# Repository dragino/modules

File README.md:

Modules
=======

What you can find in this directory:

- **Hardware** - Schematic and PCB files for modules or nodes. The eagle SCH and PCB files need to be downloaded as ZIP in this directory. Otherwise there will be issue when open in Eagle.

- **Libraries** - Libraries use for modules. 
  
- **Examples** - Examples source code to shows how to use the modules/nodes.

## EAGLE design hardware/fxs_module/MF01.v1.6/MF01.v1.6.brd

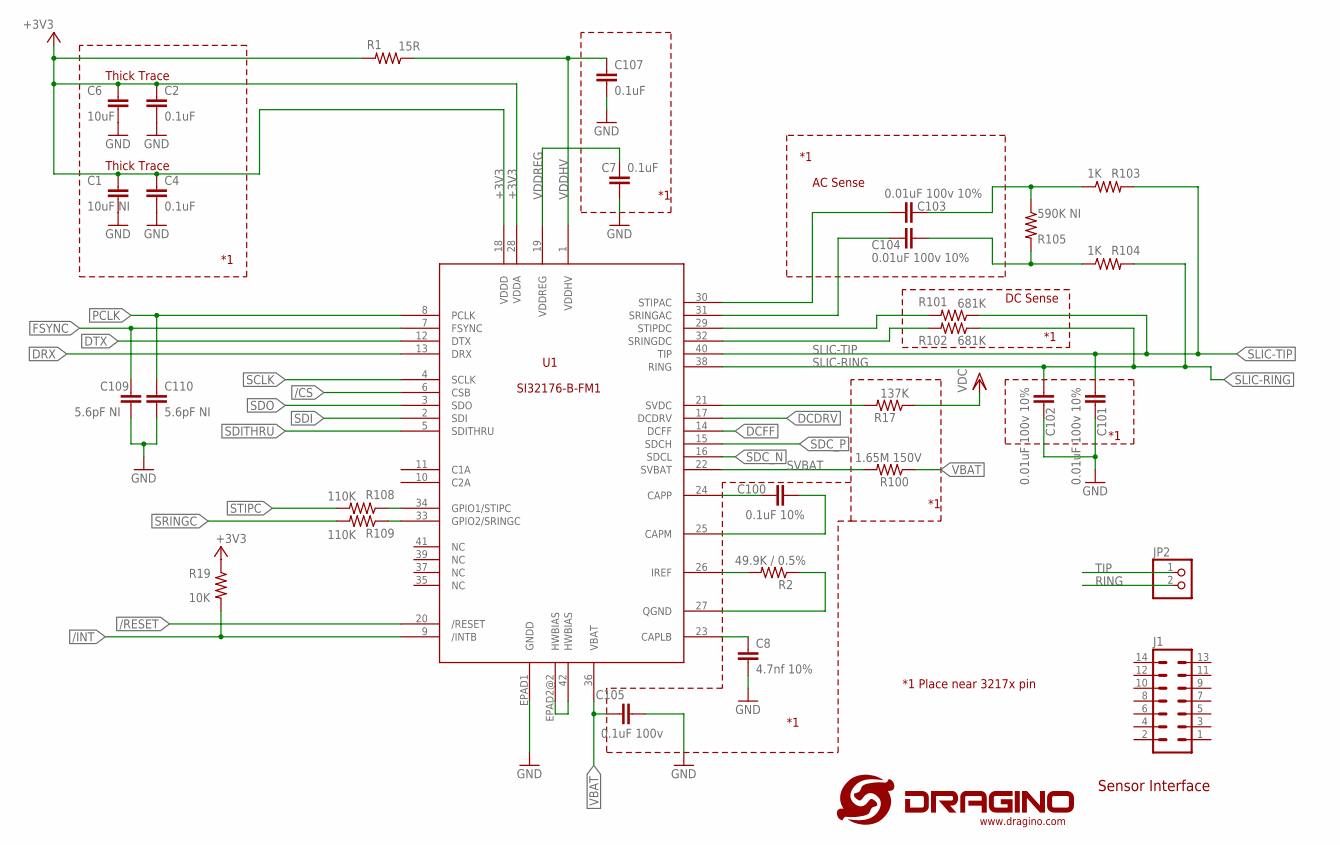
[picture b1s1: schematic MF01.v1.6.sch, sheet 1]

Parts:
C1: 10uF NI; C0603
C2, C4, C7, C107: 0.1uF; C0402
C6: 10uF; C0603
C8: 4.7nf 10%; C0402
C100: 0.1uF 10%; C0402
C101, C102, C103, C104: 0.01uF 100v 10%; C0603
C105: 0.1uF 100v; C0603
C109, C110: 5.6pF NI; C0402
J1: MA07-2
JP2: PINHD-1X2; 1X02
R1: 15R; R0805
R2: 49.9K / 0.5%; R0402
R17: 137K; R0402
R19: 10K; R0402
R100: 1.65M 150V; R0805
R101, R102: 681K; R0805
R103, R104: 1K; R0603
R105: 590K NI; R0805
R108, R109: 110K; R0402
U1: SI32176-B-FM1; SI3217X-QFN42

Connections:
+3V3: C1.2, C2.2, C4.2, C6.2, R1.2, R19.1, U1.18 (VDDD), U1.28 (VDDA); also elsewhere on the board
/CS: U1.6 (CSB); also elsewhere on the board
/INT: R19.2, U1.9 (/INTB); also elsewhere on the board
/RESET: U1.20 (/RESET); also elsewhere on the board
DCDRV: U1.17 (DCDRV); also elsewhere on the board
DCFF: U1.14 (DCFF); also elsewhere on the board
DRX: U1.13 (DRX); also elsewhere on the board
DTX: U1.12 (DTX); also elsewhere on the board
EPAD2: U1.42 (HWBIAS), U1.EPAD2@2 (HWBIAS)
FSYNC: C109.2, U1.7 (FSYNC); also elsewhere on the board
GND: C1.1, C2.1, C4.1, C6.1, C7.1, C8.2, C101.2, C102.2, C105.1, C107.1, C109.1, C110.1, U1.EPAD1 (GNDD); also elsewhere on the board
unnamed: R102.2, U1.32 (SRINGDC)
unnamed: R2.2, U1.26 (IREF)
unnamed: C8.1, U1.23 (CAPLB)
unnamed: R2.1, U1.27 (QGND)
unnamed: C100.1, U1.24 (CAPP)
unnamed: C100.2, U1.25 (CAPM)
unnamed: R101.2, U1.29 (STIPDC)
unnamed: C104.1, U1.31 (SRINGAC)
unnamed: C103.1, U1.30 (STIPAC)
unnamed: C104.2, R104.1, R105.2
unnamed: C103.2, R103.1, R105.1
unnamed: R17.2, U1.21 (SVDC)
unnamed: R108.1, U1.34 (GPIO1/STIPC)
unnamed: R109.1, U1.33 (GPIO2/SRINGC)
PCLK: C110.2, U1.8 (PCLK); also elsewhere on the board
RING: JP2.2; also elsewhere on the board
SCLK: U1.4 (SCLK); also elsewhere on the board
SDC_N: U1.16 (SDCL); also elsewhere on the board
SDC_P: U1.15 (SDCH); also elsewhere on the board
SDI: U1.2 (SDI); also elsewhere on the board
SDITHRU: U1.5 (SDITHRU)
SDO: U1.3 (SDO); also elsewhere on the board
SLIC-RING: C102.1, R102.1, R104.2, U1.38 (RING); also elsewhere on the board
SLIC-TIP: C101.1, R101.1, R103.2, U1.40 (TIP); also elsewhere on the board
SRINGC: R109.2; also elsewhere on the board
STIPC: R108.2; also elsewhere on the board
SVBAT: R100.2, U1.22 (SVBAT)
TIP: JP2.1; also elsewhere on the board
VBAT: C105.2, R100.1, U1.36 (VBAT); also elsewhere on the board
VDC: R17.1; also elsewhere on the board
VDDHV: C107.2, R1.1, U1.1 (VDDHV)
VDDREG: C7.2, U1.19 (VDDREG)

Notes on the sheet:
Sensor Interface
*1 Place near 3217x pin
DC Sense
AC Sense
Thick Trace

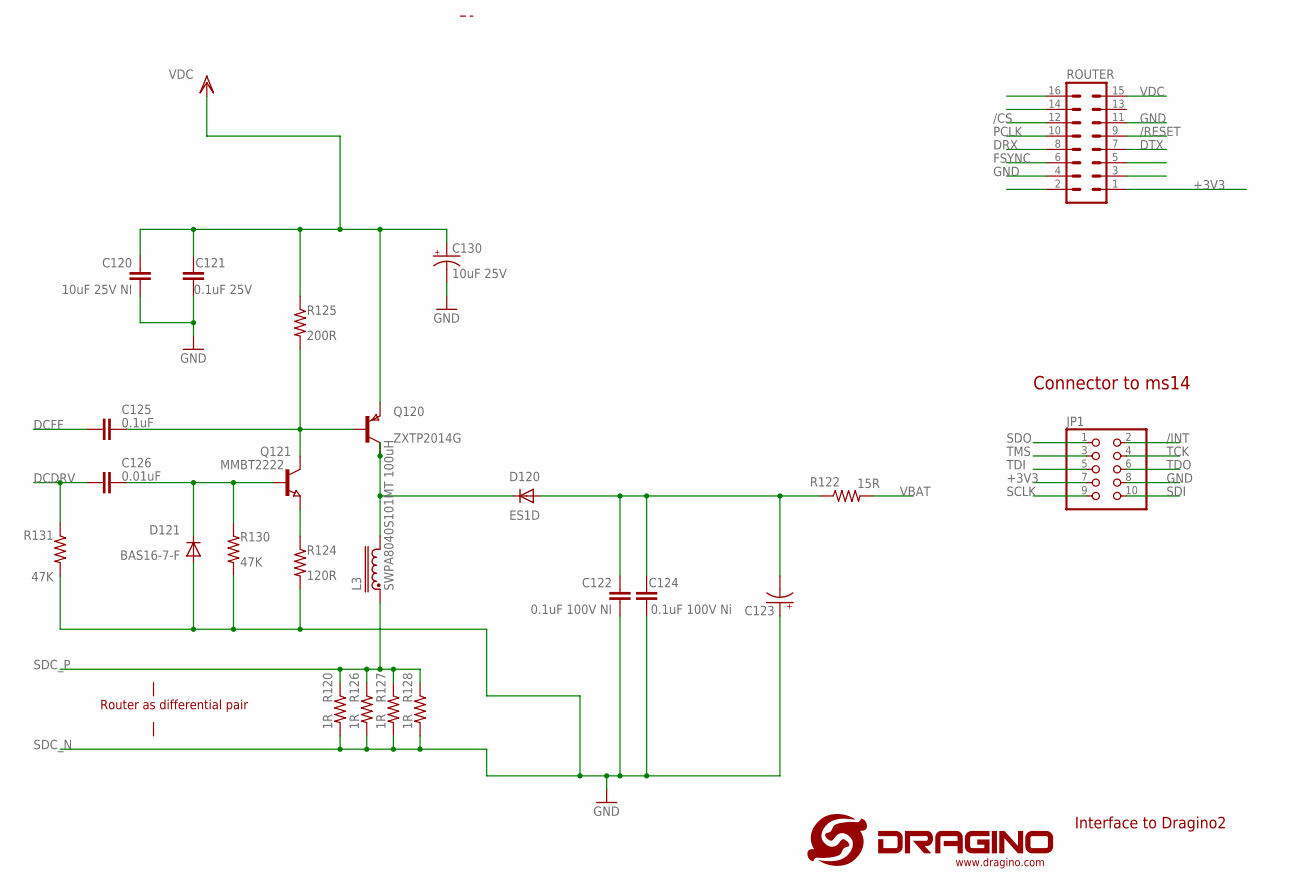
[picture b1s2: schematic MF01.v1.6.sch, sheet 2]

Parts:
C120: 10uF 25V NI; C1206
C121: 0.1uF 25V; C0402
C122: 0.1uF 100V NI; C0603
C123: CPOL-US153CLV-0605; 153CLV-0605
C124: 0.1uF 100V Ni; C0603
C125: 0.1uF; C0402
C126: 0.01uF; C0402
C130: 10uF 25V; UD-4X5,8_NICHICON
D120: ES1D; SOD-123_MINI-SMA
D121: BAS16-7-F; SOT23
JP1: PINHD-2X5_2.00; 2X05M
L3: SWPA8040S101MT 100uH; LVS808040
Q120: ZXTP2014G; SOT223
Q121: MMBT2222; SOT23
R120, R126, R127, R128: 1R; R0402
R122: 15R; R0805
R124: 120R; R0402
R125: 200R; R0603
R130, R131: 47K; R0402
ROUTER: MA08-2
U$5: LOGO-NEW; LOGO-SILK-NEW

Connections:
+3V3: JP1.7, ROUTER.1; also elsewhere on the board
/CS: ROUTER.12; also elsewhere on the board
/INT: JP1.2; also elsewhere on the board
/RESET: ROUTER.9; also elsewhere on the board
DCDRV: C126.2, R131.1; also elsewhere on the board
DCFF: C125.2; also elsewhere on the board
DRX: ROUTER.8; also elsewhere on the board
DTX: ROUTER.7; also elsewhere on the board
FSYNC: ROUTER.6; also elsewhere on the board
GND: C120.2, C121.2, C122.2, C123.+, C124.2, C130.-, D121.1 (A), JP1.8, R124.2, R130.2, R131.2, ROUTER.4, ROUTER.11; also elsewhere on the board
unnamed: C126.1, D121.3 (C), Q121.1 (B), R130.1
unnamed: Q121.2 (E), R124.1
unnamed: C125.1, Q120.1 (B), Q121.3 (C), R125.2
unnamed: D120.C, L3.P$2 (4), Q120.2 (C), Q120.4 (C)
unnamed: C122.1, C123.-, C124.1, D120.A, R122.1
PCLK: ROUTER.10; also elsewhere on the board
SCLK: JP1.9; also elsewhere on the board
SDC_N: R120.2, R126.2, R127.2, R128.2; also elsewhere on the board
SDC_P: L3.P$1 (1), R120.1, R126.1, R127.1, R128.1; also elsewhere on the board
SDI: JP1.10; also elsewhere on the board
SDO: JP1.1; also elsewhere on the board
TCK: JP1.4
TDI: JP1.5
TDO: JP1.6
TMS: JP1.3
VBAT: R122.2; also elsewhere on the board
VDC: C120.1, C121.1, C130.+, Q120.3 (E), R125.1, ROUTER.15; also elsewhere on the board

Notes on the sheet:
Interface to Dragino2
Connector to ms14
Router as differential pair

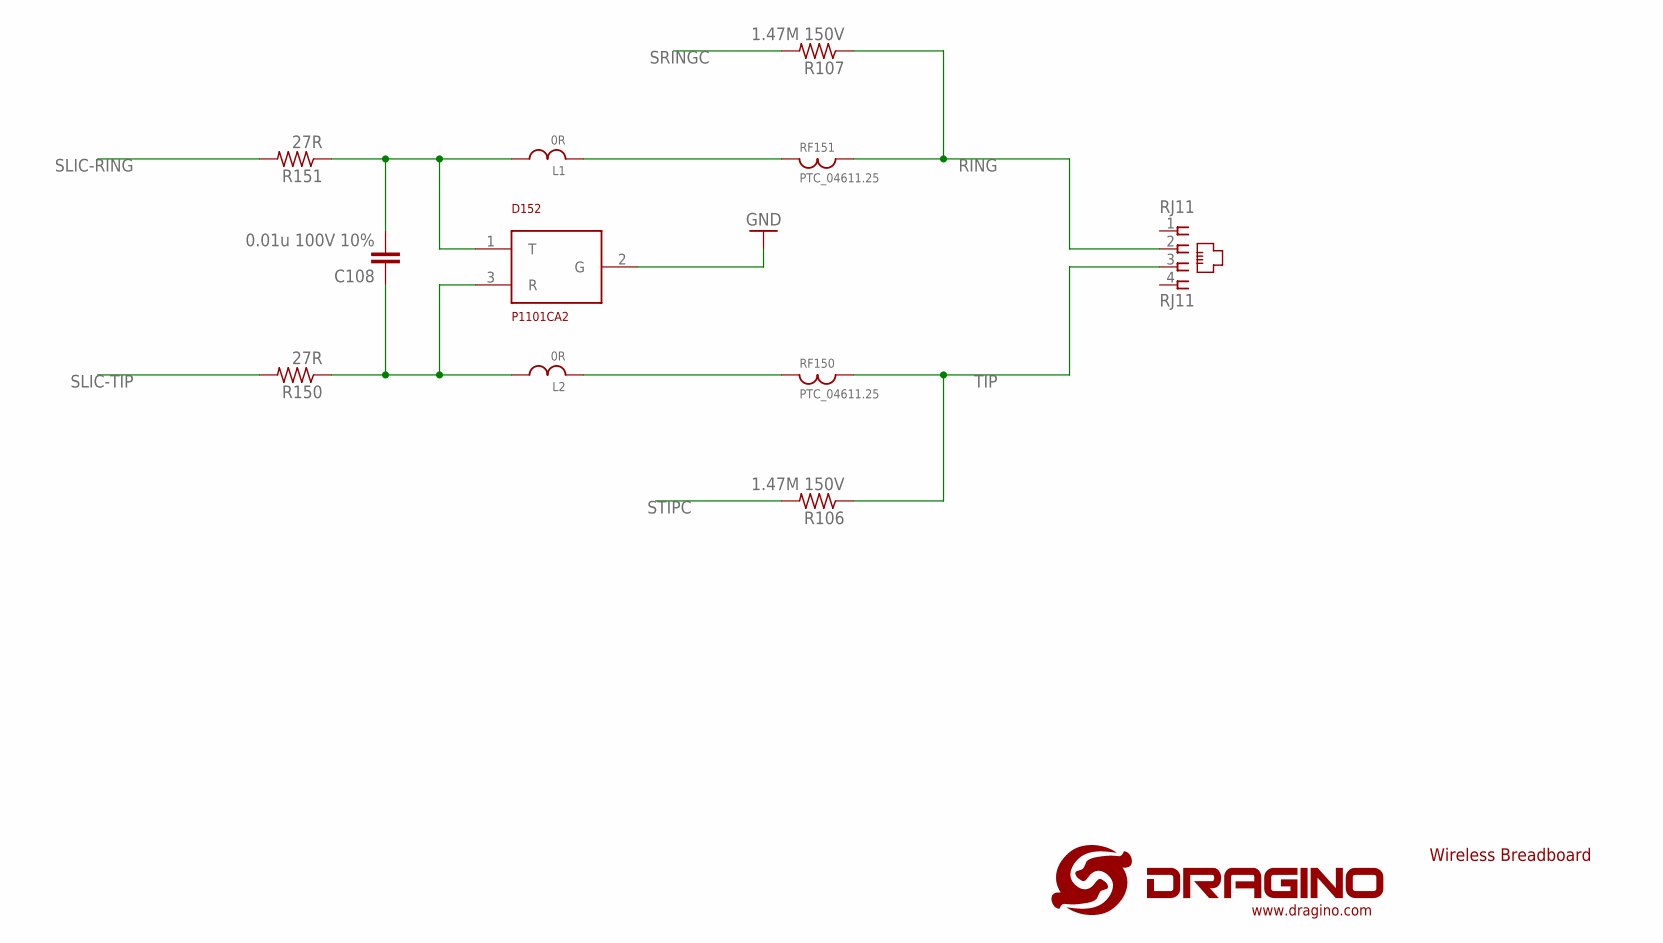
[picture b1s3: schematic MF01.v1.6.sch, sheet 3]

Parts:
C108: 0.01u 100V 10%; C0603
D152: P1101CA2; DO-214
L1, L2: 0R; C0805
R106, R107: 1.47M 150V; R1206
R150, R151: 27R; R0805
RF150, RF151: PTC_04611.25; 04611.25
RJ11: RJ11; 14867

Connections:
GND: D152.2 (G); also elsewhere on the board
unnamed: L1.1, RF151.P1
unnamed: L2.1, RF150.P1
unnamed: C108.1, D152.3 (R), L2.2, R150.1
unnamed: C108.2, D152.1 (T), L1.2, R151.1
RING: R107.1, RF151.P2, RJ11.2; also elsewhere on the board
SLIC-RING: R151.2; also elsewhere on the board
SLIC-TIP: R150.2; also elsewhere on the board
SRINGC: R107.2; also elsewhere on the board
STIPC: R106.2; also elsewhere on the board
TIP: R106.1, RF150.P2, RJ11.3; also elsewhere on the board

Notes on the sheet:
Wireless Breadboard

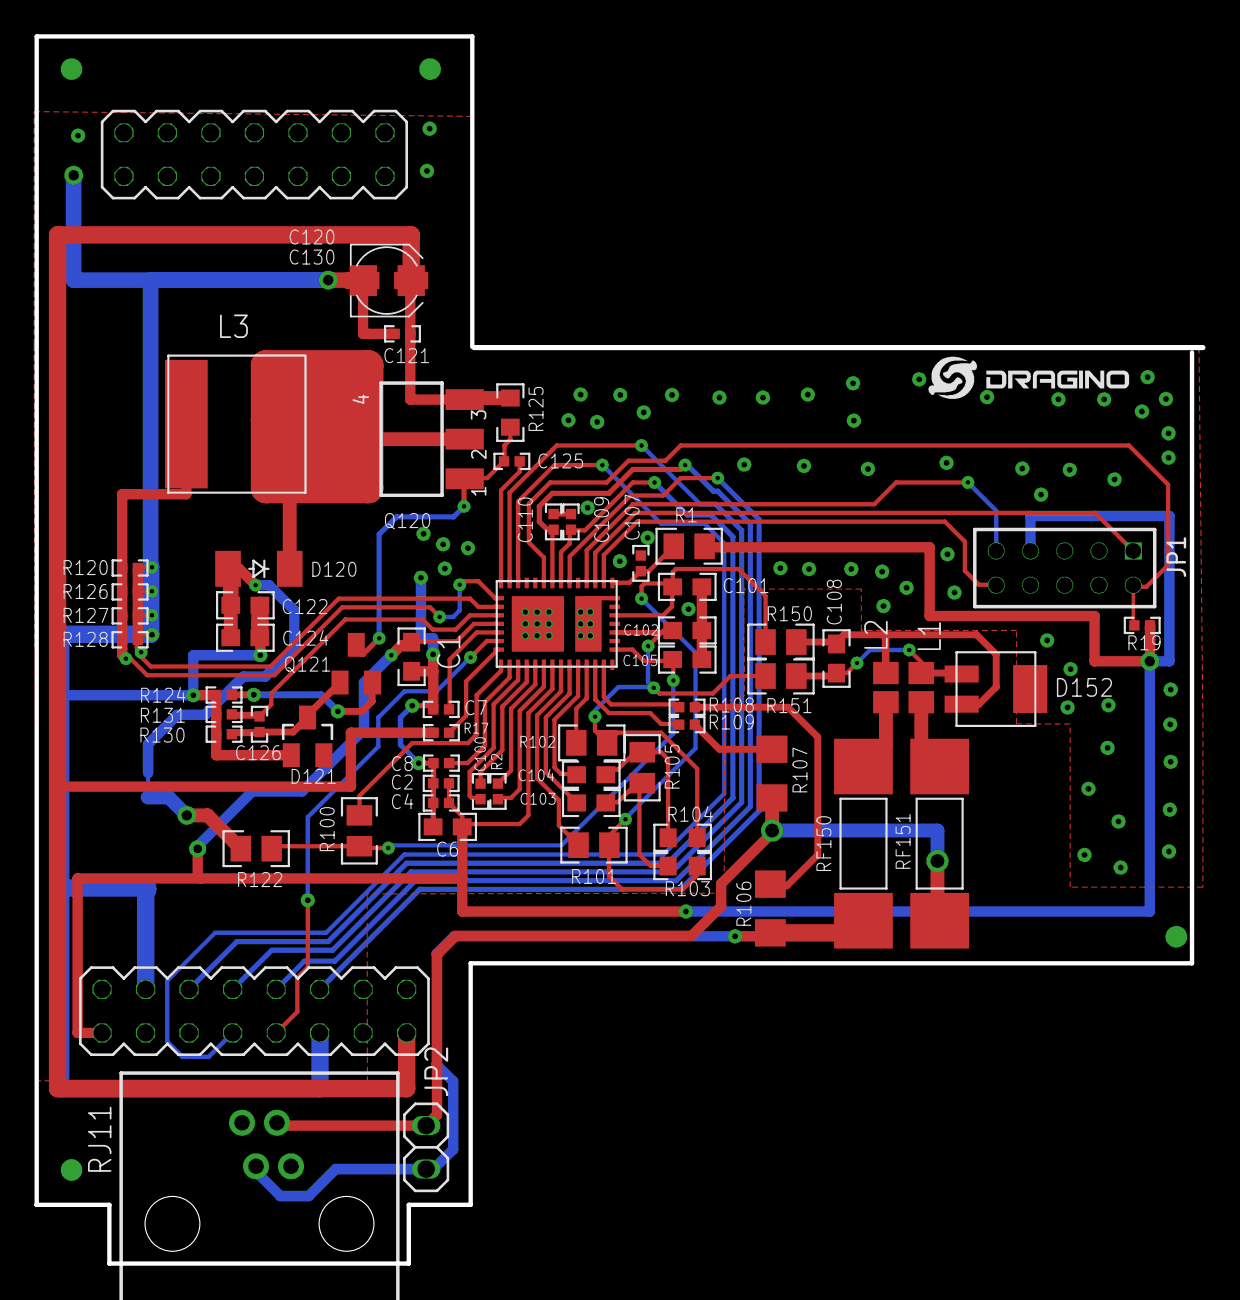
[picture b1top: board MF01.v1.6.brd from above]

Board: 2 copper layers, 68.1 x 71.6 mm, 66 parts (1 on the bottom side), 51 nets.

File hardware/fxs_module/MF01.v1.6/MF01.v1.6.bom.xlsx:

Part | Value | Device | Package
C1 | 10uF NI | C-EUC0603 | C0603
C2 | 0.1uF | C-EUC0402 | C0402
C4 | 0.1uF | C-EUC0402 | C0402
C6 | 10uF | C-EUC0603 | C0603
C7 | 0.1uF | C-EUC0402 | C0402
C8 | 4.7nf 10% | C-EUC0402 | C0402
C100 | 0.1uF 10% | C-EUC0402 | C0402
C101 | 0.01uF 100v 10% | C-EUC0603 | C0603
C102 | 0.01uF 100v 10% | C-EUC0603 | C0603
C103 | 0.01uF 100v 10% | C-EUC0603 | C0603
C104 | 0.01uF 100v 10% | C-EUC0603 | C0603
C105 | 0.1uF 100v | C-EUC0603 | C0603
C107 | 0.1uF | C-EUC0402 | C0402
C108 | 0.01u 100V 10% | C-EUC0603 | C0603
C109 | 5.6pF NI | C-EUC0402 | C0402
C110 | 5.6pF NI | C-EUC0402 | C0402
C120 | 10uF 25V NI | C-EUC1206 | C1206
C121 | 0.1uF 25V | C-EUC0402 | C0402
C122 | 0.1uF 100V NI | C-EUC0603 | C0603
C123 |  | CPOL-US153CLV-0605 | 153CLV-0605
C124 | 0.1uF 100V Ni | C-EUC0603 | C0603
C125 | 0.1uF | C-EUC0402 | C0402
C126 | 0.01uF | C-EUC0402 | C0402
C130 | 10uF 25V | CPOL-USUD-4X5 8 | UD-4X5 8_NICHICON
D120 | ES1D | CGRM4001-G | SOD-123_MINI-SMA
D121 | BAS16-7-F | BAS16-7-F | SOT23
D152 | P1101CA2 | SLIC_PROTECTORP1101CA2 | DO-214
J1 |  | MA07-2 | MA07-2
JP1 |  | PINHD-2X5_2.00 | 2X05M
JP2 |  | PINHD-1X2 | 1X02
L1 | 0R | BEADS0805 | C0805
L2 | 0R | BEADS0805 | C0805
L3 | SWPA8040S101MT 100uH | INDUCTORLVS808040 | LVS808040
Q120 | ZXTP2014G | PNPSOT223 | SOT223
Q121 | MMBT2222 | NPN-TRANSISTOR_SOT23 | SOT23
R1 | 15R | R-US_R0805 | R0805
R2 | 49.9K / 0.5% | R-US_R0402 | R0402
R17 | 137K | R-US_R0402 | R0402
R19 | 10K | R-US_R0402 | R0402
R100 | 1.65M 150V | R-US_R0805 | R0805
R101 | 681K | R-US_R0805 | R0805
R102 | 681K | R-US_R0805 | R0805
R103 | 1K | R-US_R0603 | R0603
R104 | 1K | R-US_R0603 | R0603
R105 | 590K NI | R-US_R0805 | R0805
R106 | 1.47M 150V | R-US_R1206 | R1206
R107 | 1.47M 150V | R-US_R1206 | R1206
R108 | 110K | R-US_R0402 | R0402
R109 | 110K | R-US_R0402 | R0402
R120 | 1R | R-US_R0402 | R0402
R122 | 15R | R-US_R0805 | R0805
R124 | 120R | R-US_R0402 | R0402
R125 | 200R | R-US_R0603 | R0603
R126 | 1R | R-US_R0402 | R0402
R127 | 1R | R-US_R0402 | R0402
R128 | 1R | R-US_R0402 | R0402
R130 | 47K | R-US_R0402 | R0402
R131 | 47K | R-US_R0402 | R0402
R150 | 27R | R-US_R0805 | R0805
R151 | 27R | R-US_R0805 | R0805
RF150 | PTC_04611.25 | PTC_04611.25 | 4611.25
RF151 | PTC_04611.25 | PTC_04611.25 | 4611.25
RJ11 | RJ11 | 14867RJ11 | 14867
ROUTER |  | MA08-2 | MA08-2
U1 | SI32176-B-FM1 | SI3217X | SI3217X-QFN42

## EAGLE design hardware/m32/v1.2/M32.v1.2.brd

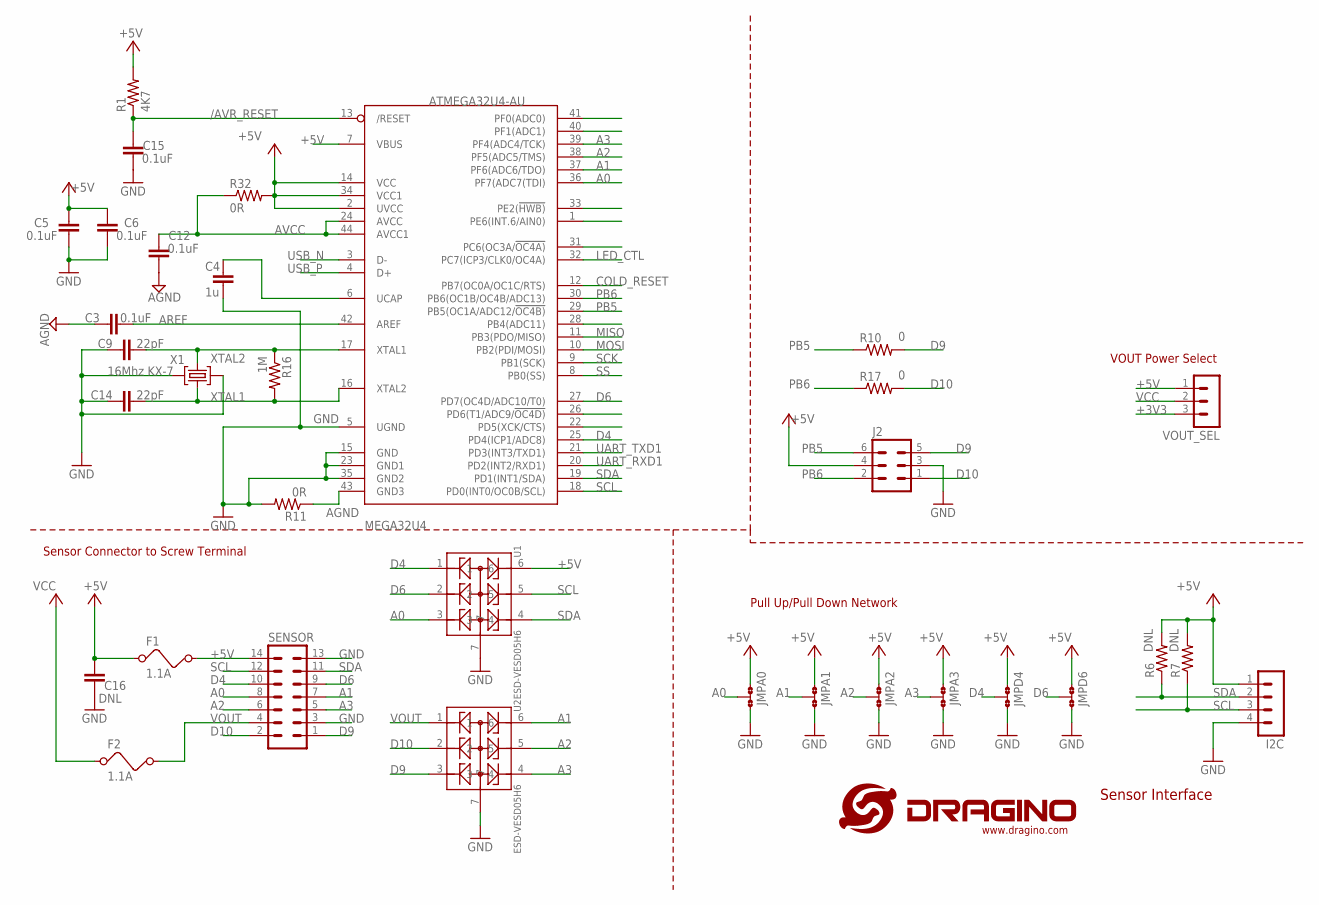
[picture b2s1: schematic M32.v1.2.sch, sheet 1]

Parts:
C3, C5, C6, C12, C15: 0.1uF; C0402
C4: 1u; C0402
C9, C14: 22pF; C0402
C16: DNL; C0402
F1, F2: 1.1A; L1812
I2C: MA04-1
J2: MA03-2
JMPA0, JMPA1, JMPA2, JMPA3: JUM-A2; A0R-JMP
JMPD4, JMPD6: JUM-A2; A0R-JMP
MEGA32U4: ATMEGA32U4-AU; TQFP44
R1: 4K7; R0402
R6, R7: DNL; R0603
R10, R17: 0; R0603
R11: 0R; R0603
R16: 1M; R0402
R32: 0R; R0402
SENSOR: MA07-2
U1, U2: ESD-VESD05H6; VESD05A6
VOUT_SEL: MA03-1
X1: 16Mhz KX-7; CRYSTAL-3.2-2.5

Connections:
32U4_A4: MEGA32U4.40 (PF1(ADC1)); also elsewhere on the board
32U4_A5: MEGA32U4.41 (PF0(ADC0)); also elsewhere on the board
+3V3: VOUT_SEL.3; also elsewhere on the board
+5V: C5.1, C6.1, C16.1, F1.1, I2C.1, J2.4, JMPA0.3, JMPA1.3, JMPA2.3, JMPA3.3, JMPD4.3, JMPD6.3, MEGA32U4.2 (UVCC), MEGA32U4.7 (VBUS), MEGA32U4.14 (VCC), MEGA32U4.34 (VCC1), R1.2, R6.2, R7.2, R32.2, U1.6, VOUT_SEL.1; also elsewhere on the board
/AVR_RESET: C15.1, MEGA32U4.13 (/RESET), R1.1; also elsewhere on the board
A0: JMPA0.2, MEGA32U4.36 (PF7(ADC7(TDI)), SENSOR.8, U1.3; also elsewhere on the board
A1: JMPA1.2, MEGA32U4.37 (PF6(ADC6/TDO)), SENSOR.7, U2.6; also elsewhere on the board
A2: JMPA2.2, MEGA32U4.38 (PF5(ADC5/TMS)), SENSOR.6, U2.5; also elsewhere on the board
A3: JMPA3.2, MEGA32U4.39 (PF4(ADC4/TCK)), SENSOR.5, U2.4; also elsewhere on the board
AGND: C3.1, MEGA32U4.43 (GND3), R11.1; also elsewhere on the board
AREF: C3.2, MEGA32U4.42 (AREF); also elsewhere on the board
AVCC: C12.1, MEGA32U4.24 (AVCC), MEGA32U4.44 (AVCC1), R32.1; also elsewhere on the board
COLD_RESET: MEGA32U4.12 (PB7(OC0A/OC1C/RTS)); also elsewhere on the board
D4: JMPD4.2, MEGA32U4.25 (PD4(ICP1/ADC8)), SENSOR.10, U1.1; also elsewhere on the board
D6: JMPD6.2, MEGA32U4.27 (PD7(OC4D/ADC10/T0)), SENSOR.9, U1.2; also elsewhere on the board
D9: J2.5, R10.2, SENSOR.1, U2.3
D10: J2.1, R17.2, SENSOR.2, U2.2
GND: C4.1, C5.2, C6.2, C9.1, C14.1, C15.2, C16.2, I2C.4, J2.3, JMPA0.1, JMPA1.1, JMPA2.1, JMPA3.1, JMPD4.1, JMPD6.1, MEGA32U4.5 (UGND), MEGA32U4.15 (GND), MEGA32U4.23 (GND1), MEGA32U4.35 (GND2), R11.2, SENSOR.3, SENSOR.13, U1.7, U2.7, X1.2 (GND), X1.4 (GND); also elsewhere on the board
GND1: C12.2
LED_CTL: MEGA32U4.32 (PC7(ICP3/CLK0/OC4A)); also elsewhere on the board
MISO: MEGA32U4.11 (PB3(PDO/MISO)); also elsewhere on the board
MOSI: MEGA32U4.10 (PB2(PDI/MOSI)); also elsewhere on the board
unnamed: F1.2, SENSOR.14
unnamed 31: C4.2, MEGA32U4.6 (UCAP); also elsewhere on the board
PB4: MEGA32U4.28 (PB4(ADC11)); also elsewhere on the board
PB5: J2.6, MEGA32U4.29 (PB5(OC1A/ADC12/!OC4B)), R10.1; also elsewhere on the board
PB6: J2.2, MEGA32U4.30 (PB6(OC1B/OC4B/ADC13)), R17.1; also elsewhere on the board
PC6: MEGA32U4.31 (PC6(OC3A/!OC4A)); also elsewhere on the board
PD5: MEGA32U4.22 (PD5(XCK/CTS)); also elsewhere on the board
PD6: MEGA32U4.26 (PD6(T1/ADC9/!OC4D)); also elsewhere on the board
PE2: MEGA32U4.33 (PE2(!HWB)); also elsewhere on the board
PE6: MEGA32U4.1 (PE6(INT.6/AIN0)); also elsewhere on the board
SCK: MEGA32U4.9 (PB1(SCK)); also elsewhere on the board
SCL: I2C.3, MEGA32U4.18 (PD0(INT0/OC0B/SCL)), R7.1, SENSOR.12, U1.5; also elsewhere on the board
SDA: I2C.2, MEGA32U4.19 (PD1(INT1/SDA)), R6.1, SENSOR.11, U1.4; also elsewhere on the board
SS: MEGA32U4.8 (PB0(SS)); also elsewhere on the board
UART_RXD1: MEGA32U4.20 (PD2(INT2/RXD1)); also elsewhere on the board
UART_TXD1: MEGA32U4.21 (PD3(INT3/TXD1)); also elsewhere on the board
USB_N: MEGA32U4.3 (D-); also elsewhere on the board
USB_P: MEGA32U4.4 (D+); also elsewhere on the board
VCC: F2.1, VOUT_SEL.2
VOUT: F2.2, SENSOR.4, U2.1
XTAL1: C14.2, MEGA32U4.16 (XTAL2), R16.2, X1.3 (C2); also elsewhere on the board
XTAL2: C9.2, MEGA32U4.17 (XTAL1), R16.1, X1.1 (C1); also elsewhere on the board

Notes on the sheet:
Sensor Interface
VOUT Power Select
Pull Up/Pull Down Network
Sensor Connector to Screw Terminal

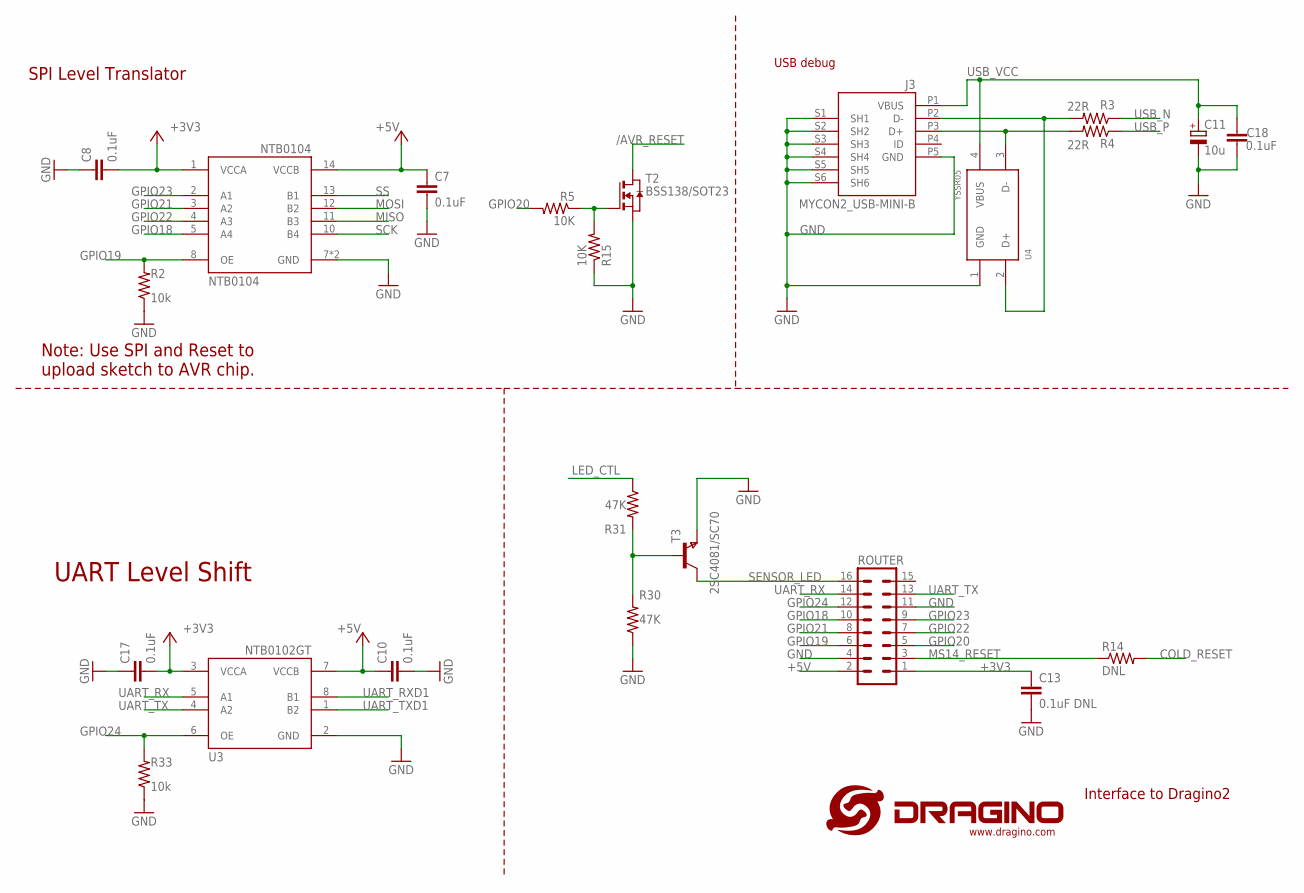
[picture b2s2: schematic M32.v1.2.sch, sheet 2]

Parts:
C7, C8, C10, C17, C18: 0.1uF; C0402
C11: 10u; SMC_B
C13: 0.1uF DNL; C0402
J3: MYCON2_USB-MINI-B; CON2_USB_MICRO_B_AT
NTB0104: NTB0104; DHVQFN14
R2, R33: 10k; R0402
R3, R4: 22R; R0402
R5, R15: 10K; R0402
R14: DNL; R0402
R30, R31: 47K; R0402
ROUTER: MA08-2
T2: BSS138/SOT23; SOT-23
T3: 2SC4081/SC70; SOT323
U3: NTB0102GT; NXP-SOT833-1
U4: YSSR05; SOT143
U$5: LOGO-NEW; LOGO-SILK-NEW

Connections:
+3V3: C8.2, C13.1, C17.2, NTB0104.1 (VCCA), ROUTER.1, U3.3 (VCCA); also elsewhere on the board
+5V: C7.1, C10.1, NTB0104.14 (VCCB), ROUTER.2, U3.7 (VCCB); also elsewhere on the board
/AVR_RESET: T2.1 (D); also elsewhere on the board
COLD_RESET: R14.2; also elsewhere on the board
GND: C7.2, C8.1, C10.2, C11.-, C13.2, C17.1, C18.2, J3.P5 (GND), J3.S1 (SH1), J3.S2 (SH2), J3.S3 (SH3), J3.S4 (SH4), J3.S5 (SH5), J3.S6 (SH6), NTB0104.7 (GND), NTB0104.EXP (GND), R2.1, R15.1, R30.1, R33.1, ROUTER.4, ROUTER.11, T2.2 (S), T3.3 (E), U3.2 (GND), U4.1 (GND); also elsewhere on the board
GPIO18: NTB0104.5 (A4), ROUTER.10
GPIO19: NTB0104.8 (OE), R2.2, ROUTER.6
GPIO20: R5.2, ROUTER.5
GPIO21: NTB0104.3 (A2), ROUTER.8
GPIO22: NTB0104.4 (A3), ROUTER.7
GPIO23: NTB0104.2 (A1), ROUTER.9
GPIO24: R33.2, ROUTER.12, U3.6 (OE)
LED_CTL: R31.1; also elsewhere on the board
MISO: NTB0104.11 (B3); also elsewhere on the board
MOSI: NTB0104.12 (B2); also elsewhere on the board
MS14_RESET: R14.1, ROUTER.3
unnamed: R5.1, R15.2, T2.3 (G)
unnamed: R30.2, R31.2, T3.2 (B)
SCK: NTB0104.10 (B4); also elsewhere on the board
SENSOR_LED: ROUTER.16, T3.1 (C)
SS: NTB0104.13 (B1); also elsewhere on the board
UART_RX: ROUTER.14, U3.5 (A1)
UART_RXD1: U3.8 (B1); also elsewhere on the board
UART_TX: ROUTER.13, U3.4 (A2)
UART_TXD1: U3.1 (B2); also elsewhere on the board
USB1_N: J3.P2 (D-), R3.2, U4.2 (D+)
USB1_P: J3.P3 (D+), R4.2, U4.3 (D-)
USB_N: R3.1; also elsewhere on the board
USB_P: R4.1; also elsewhere on the board
USB_VCC: C11.+, C18.1, J3.P1 (VBUS), U4.4 (VBUS)

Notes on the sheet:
UART Level Shift
SPI Level Translator
Interface to Dragino2
Note: Use SPI and Reset to upload sketch to AVR chip.
USB debug

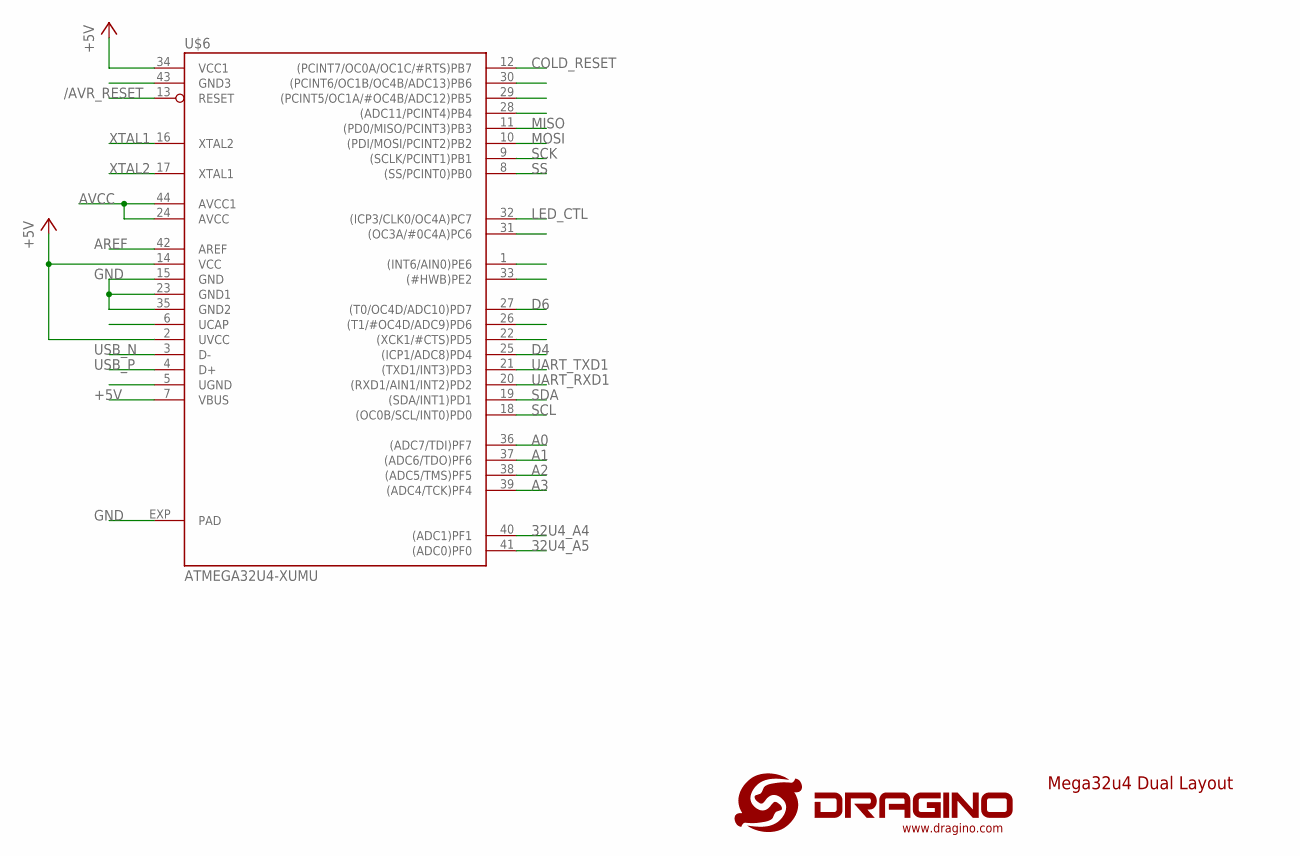
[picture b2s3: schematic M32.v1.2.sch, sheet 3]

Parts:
U$6: ATMEGA32U4-XUMU; QFN44ML7X7

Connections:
32U4_A4: U$6.40 ((ADC1)PF1); also elsewhere on the board
32U4_A5: U$6.41 ((ADC0)PF0); also elsewhere on the board
+5V: U$6.2 (UVCC), U$6.7 (VBUS), U$6.14 (VCC), U$6.34 (VCC1); also elsewhere on the board
/AVR_RESET: U$6.13 (RESET); also elsewhere on the board
A0: U$6.36 ((ADC7/TDI)PF7); also elsewhere on the board
A1: U$6.37 ((ADC6/TDO)PF6); also elsewhere on the board
A2: U$6.38 ((ADC5/TMS)PF5); also elsewhere on the board
A3: U$6.39 ((ADC4/TCK)PF4); also elsewhere on the board
AGND: U$6.43 (GND3); also elsewhere on the board
AREF: U$6.42 (AREF); also elsewhere on the board
AVCC: U$6.24 (AVCC), U$6.44 (AVCC1); also elsewhere on the board
COLD_RESET: U$6.12 ((PCINT7/OC0A/OC1C/#RTS)PB7); also elsewhere on the board
D4: U$6.25 ((ICP1/ADC8)PD4); also elsewhere on the board
D6: U$6.27 ((T0/OC4D/ADC10)PD7); also elsewhere on the board
GND: U$6.5 (UGND), U$6.15 (GND), U$6.23 (GND1), U$6.35 (GND2), U$6.EXP (PAD); also elsewhere on the board
LED_CTL: U$6.32 ((ICP3/CLK0/OC4A)PC7); also elsewhere on the board
MISO: U$6.11 ((PD0/MISO/PCINT3)PB3); also elsewhere on the board
MOSI: U$6.10 ((PDI/MOSI/PCINT2)PB2); also elsewhere on the board
unnamed 31: U$6.6 (UCAP); also elsewhere on the board
PB4: U$6.28 ((ADC11/PCINT4)PB4); also elsewhere on the board
PB5: U$6.29 ((PCINT5/OC1A/#OC4B/ADC12)PB5); also elsewhere on the board
PB6: U$6.30 ((PCINT6/OC1B/OC4B/ADC13)PB6); also elsewhere on the board
PC6: U$6.31 ((OC3A/#0C4A)PC6); also elsewhere on the board
PD5: U$6.22 ((XCK1/#CTS)PD5); also elsewhere on the board
PD6: U$6.26 ((T1/#OC4D/ADC9)PD6); also elsewhere on the board
PE2: U$6.33 ((#HWB)PE2); also elsewhere on the board
PE6: U$6.1 ((INT6/AIN0)PE6); also elsewhere on the board
SCK: U$6.9 ((SCLK/PCINT1)PB1); also elsewhere on the board
SCL: U$6.18 ((OC0B/SCL/INT0)PD0); also elsewhere on the board
SDA: U$6.19 ((SDA/INT1)PD1); also elsewhere on the board
SS: U$6.8 ((SS/PCINT0)PB0); also elsewhere on the board
UART_RXD1: U$6.20 ((RXD1/AIN1/INT2)PD2); also elsewhere on the board
UART_TXD1: U$6.21 ((TXD1/INT3)PD3); also elsewhere on the board
USB_N: U$6.3 (D-); also elsewhere on the board
USB_P: U$6.4 (D+); also elsewhere on the board
XTAL1: U$6.16 (XTAL2); also elsewhere on the board
XTAL2: U$6.17 (XTAL1); also elsewhere on the board

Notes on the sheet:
Mega32u4 Dual Layout

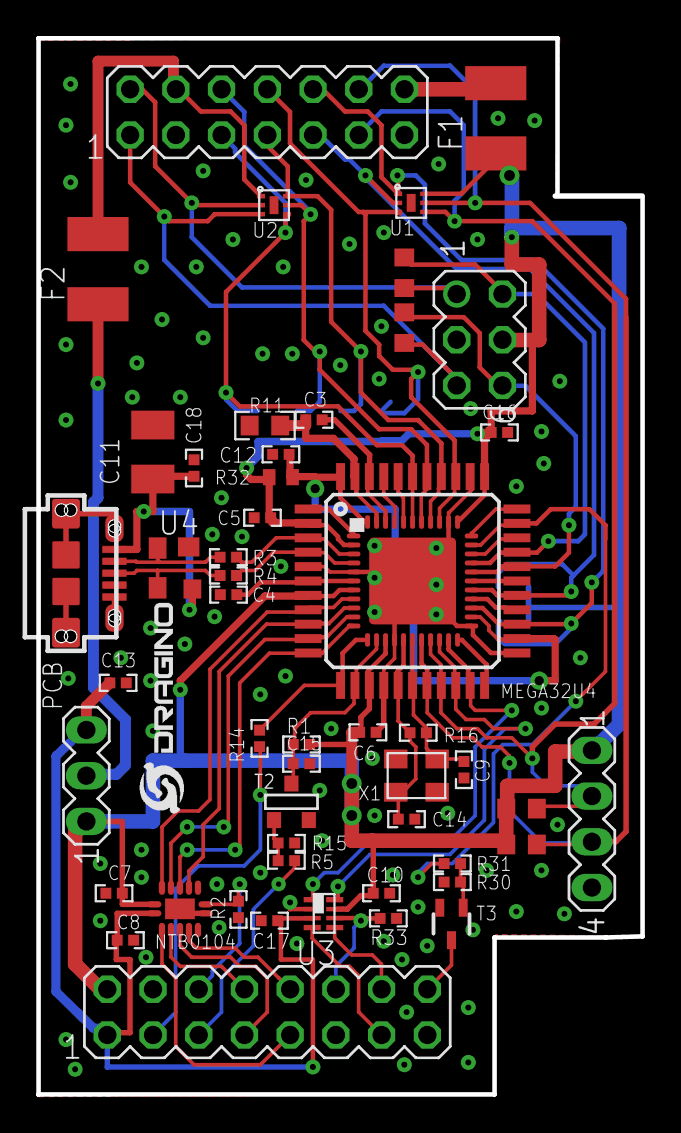
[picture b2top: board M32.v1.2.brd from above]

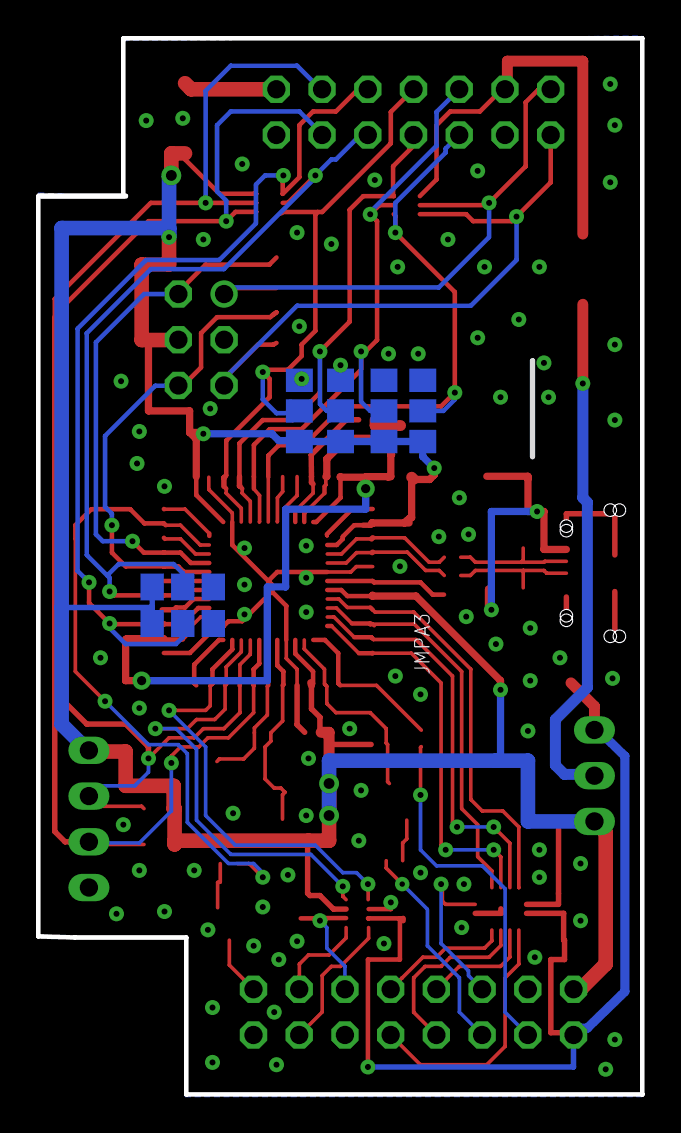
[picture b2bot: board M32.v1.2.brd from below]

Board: 2 copper layers, 33.5 x 58.6 mm, 58 parts (6 on the bottom side), 59 nets.

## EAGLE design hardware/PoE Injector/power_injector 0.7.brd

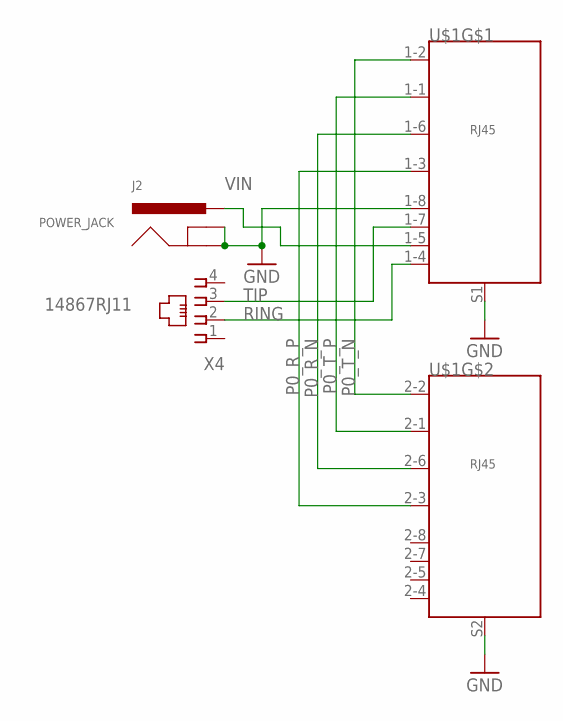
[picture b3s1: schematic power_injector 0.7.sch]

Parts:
J2: POWER_JACK; POWER_JACK_SLOT1
U$1: ETHERNET_2PORT; ETHERNET-1X2
X4: 14867RJ11; 14867

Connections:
GND: J2.GND@1 (GNDBREAK), J2.GND@2 (GND), U$1.1-8 (8), U$1.S1 (SHIELD), U$1.S2 (SHIELD)
P0_R_N: U$1.1-6 (6), U$1.2-6 (6)
P0_R_P: U$1.1-3 (3), U$1.2-3 (3)
P0_T_N: U$1.1-2 (2), U$1.2-2 (2)
P0_T_P: U$1.1-1 (1), U$1.2-1 (1)
RING: U$1.1-4 (4), X4.2
TIP: U$1.1-7 (7), X4.3
VIN: J2.PWR, U$1.1-5 (5)

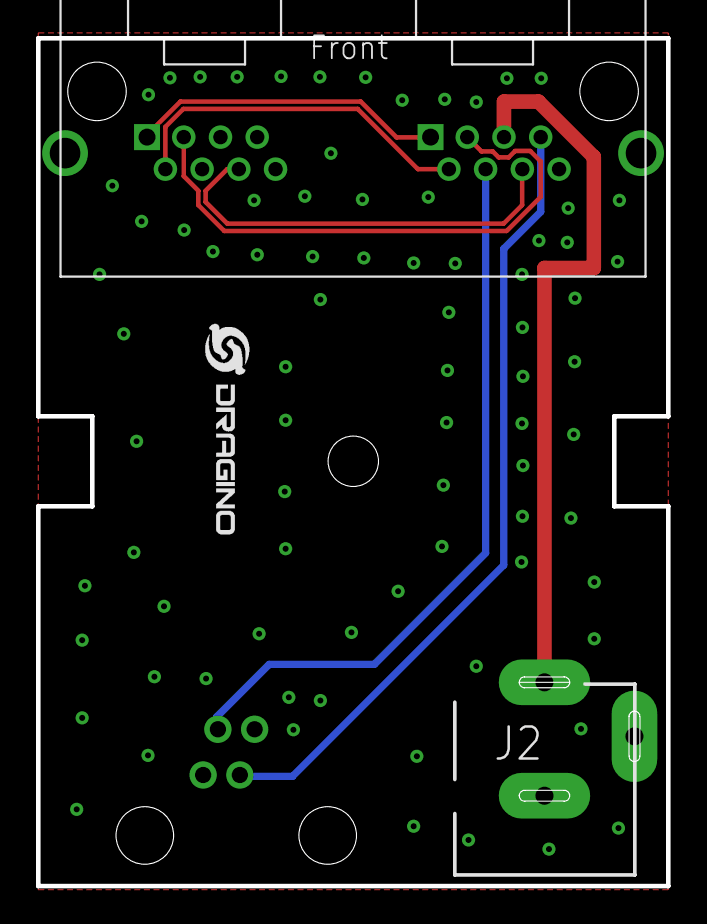
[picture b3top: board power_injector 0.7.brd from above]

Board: 2 copper layers, 35.0 x 47.1 mm, 4 parts (1 on the bottom side), 8 nets.

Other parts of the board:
U$2: LOGO-SILK-NEW

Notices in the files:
parts and their libraries:
dragino: http://creativecommons.org/licenses/by-sa/3.0
dragino: Released under the CC Attribution Share-Alike 3.0 License
SparkFun-Connectors: Licensing: Creative Commons ShareAlike 4.0 International - https://creativecommons.org/licenses/by-sa/4.0
